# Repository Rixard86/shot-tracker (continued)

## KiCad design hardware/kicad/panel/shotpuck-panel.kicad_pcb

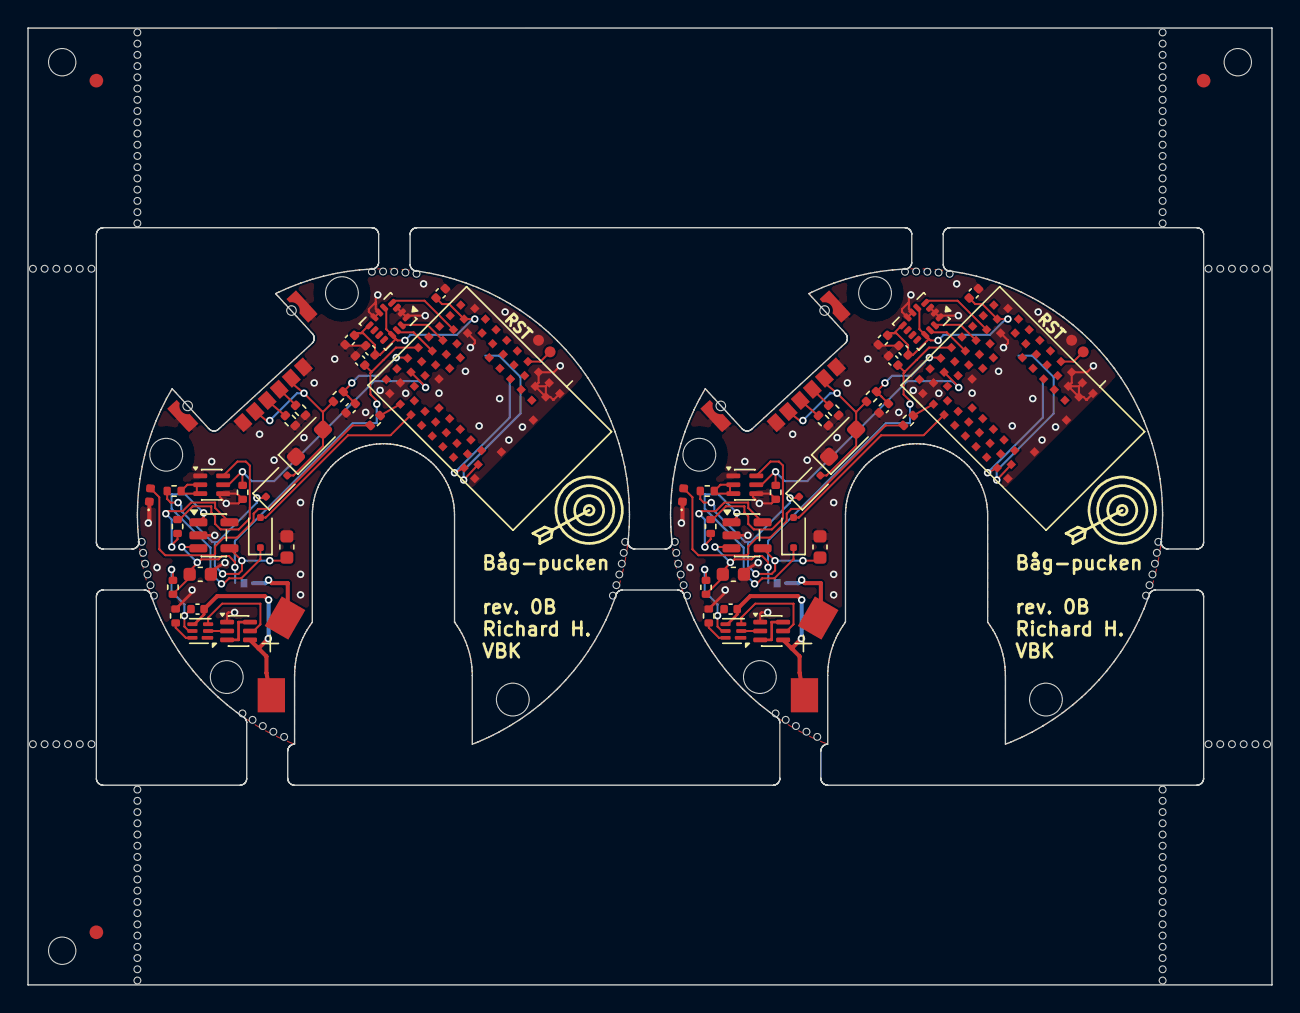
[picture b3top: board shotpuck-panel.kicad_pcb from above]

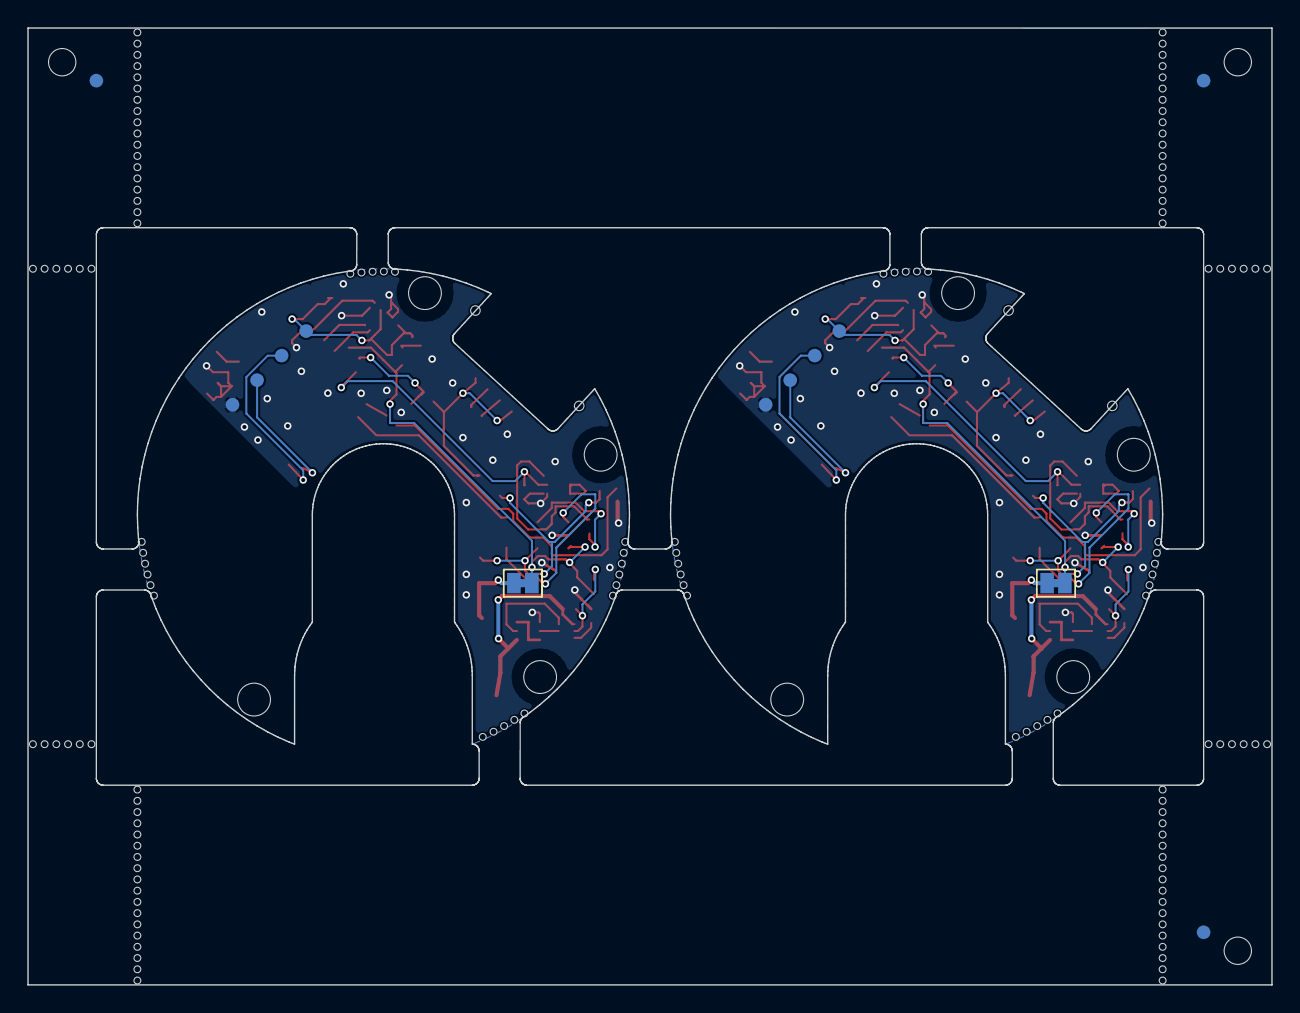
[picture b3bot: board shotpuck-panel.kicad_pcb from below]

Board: 2 copper layers, 91.0 x 70.0 mm, 221 parts (7 on the bottom side), 58 nets.

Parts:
BT1_0, BT1_1: LIR1254 (plain, spring contacts); LIR1254_Contacts_Edit
C1_0, C1_1: 4.7u 10V; C_0603_1608Metric
C2_0, C2_1: 10u 10V; C_0603_1608Metric
C3_0, C3_1, C4_0, C4_1: 4.7u 6.3V; C_0402_1005Metric
C6_0, C6_1, C7_0, C7_1, C8_0, C8_1, C9_0, C9_1: 100n; C_0402_1005Metric
D1_0, D1_1, D2_0, D2_1: BAT54J; D_SOD-323F
D3_0, D3_1: SMF5.0CA; D_SOD-123F
D4_0, D4_1: LED yellow-green 0402; LED_0402_1005Metric
H1_0, H1_1, H2_0, H2_1, H3_0, H3_1, H4_0, H4_1: M2; MountingHole_2.4mm_NPTH
J1_0, J1_1: TYPE-C 6PFS 2JCB1.6-H6.7 IPX8; USB_C_Receptacle_ShouHan_TYPE-C-6PFS-2JCB1.6-H6.7_IPX8
J2_0, J2_1: SWD pads; SWD_Pads_1x4_P2.54
JP1_0, JP1_1: I_MEAS (cut to measure); SolderJumper-2_P1.3mm_Bridged_Pad1.0x1.5mm
JP2_0, JP2_1: RESET pads; TweezerPads_2x0.8mm_Gap0.4mm
KiKit_FID_B_1, KiKit_FID_B_2, KiKit_FID_B_3: Fiducial
KiKit_FID_T_1, KiKit_FID_T_2, KiKit_FID_T_3: Fiducial
KiKit_MB_1_2, KiKit_MB_1_3, KiKit_MB_1_4, KiKit_MB_1_5, KiKit_MB_1_6, KiKit_MB_2_1, KiKit_MB_2_2, KiKit_MB_2_3, KiKit_MB_2_4, KiKit_MB_2_5, KiKit_MB_2_6, KiKit_MB_3_1, KiKit_MB_3_2, KiKit_MB_3_3, KiKit_MB_3_4, KiKit_MB_3_5, KiKit_MB_3_6, KiKit_MB_4_1, KiKit_MB_4_2, KiKit_MB_4_3, KiKit_MB_4_4, KiKit_MB_4_5, KiKit_MB_5_2, KiKit_MB_5_3, KiKit_MB_5_4, KiKit_MB_5_5, KiKit_MB_5_6, KiKit_MB_6_1, KiKit_MB_6_2, KiKit_MB_6_3, KiKit_MB_6_4, KiKit_MB_6_5, KiKit_MB_6_6, KiKit_MB_7_1, KiKit_MB_7_2, KiKit_MB_7_3, KiKit_MB_7_4, KiKit_MB_7_5, KiKit_MB_7_6, KiKit_MB_8_1, KiKit_MB_8_2, KiKit_MB_8_3, KiKit_MB_8_4, KiKit_MB_8_5, KiKit_MB_9_2, KiKit_MB_9_3, KiKit_MB_9_4, KiKit_MB_9_5, KiKit_MB_9_6, KiKit_MB_9_7, KiKit_MB_9_8, KiKit_MB_9_9, KiKit_MB_9_10, KiKit_MB_9_11, KiKit_MB_9_12, KiKit_MB_9_13, KiKit_MB_9_14, KiKit_MB_9_15, KiKit_MB_9_16, KiKit_MB_9_17, KiKit_MB_9_18, KiKit_MB_9_19, KiKit_MB_10_2, KiKit_MB_10_3, KiKit_MB_10_4, KiKit_MB_10_5, KiKit_MB_10_6, KiKit_MB_10_7, KiKit_MB_10_8, KiKit_MB_10_9, KiKit_MB_10_10, KiKit_MB_10_11, KiKit_MB_10_12, KiKit_MB_10_13, KiKit_MB_10_14, KiKit_MB_10_15, KiKit_MB_10_16, KiKit_MB_10_17, KiKit_MB_10_18, KiKit_MB_10_19, KiKit_MB_11_2, KiKit_MB_11_3, KiKit_MB_11_4, KiKit_MB_11_5, KiKit_MB_11_6, KiKit_MB_11_7, KiKit_MB_11_8, KiKit_MB_11_9, KiKit_MB_11_10, KiKit_MB_11_11, KiKit_MB_11_12, KiKit_MB_11_13, KiKit_MB_11_14, KiKit_MB_11_15, KiKit_MB_11_16, KiKit_MB_11_17, KiKit_MB_11_18, KiKit_MB_11_19, KiKit_MB_12_2, KiKit_MB_12_3, KiKit_MB_12_4, KiKit_MB_12_5, KiKit_MB_12_6, KiKit_MB_12_7, KiKit_MB_12_8, KiKit_MB_12_9, KiKit_MB_12_10, KiKit_MB_12_11, KiKit_MB_12_12, KiKit_MB_12_13, KiKit_MB_12_14, KiKit_MB_12_15, KiKit_MB_12_16, KiKit_MB_12_17, KiKit_MB_12_18, KiKit_MB_12_19, KiKit_MB_13_2, KiKit_MB_13_3, KiKit_MB_13_4, KiKit_MB_13_5, KiKit_MB_13_6, KiKit_MB_13_7, KiKit_MB_14_2, KiKit_MB_14_3, KiKit_MB_14_4, KiKit_MB_14_5, KiKit_MB_14_6, KiKit_MB_14_7, KiKit_MB_15_2, KiKit_MB_15_3, KiKit_MB_15_4, KiKit_MB_15_5, KiKit_MB_15_6, KiKit_MB_15_7, KiKit_MB_16_2, KiKit_MB_16_3, KiKit_MB_16_4, KiKit_MB_16_5, KiKit_MB_16_6, KiKit_MB_16_7: NPTH
KiKit_TO_1, KiKit_TO_2, KiKit_TO_3: NPTH
Q1_0, Q1_1: DMN63D8LDW; SOT-363_SC-70-6
Q2_0, Q2_1: DMN2004DWK; SOT-363_SC-70-6
R1_0, R1_1: 47k 1%; R_0402_1005Metric
R2_0, R2_1: 1M; R_0402_1005Metric
R3_0, R3_1: 100k; R_0402_1005Metric
R4_0, R4_1, R9_0, R9_1: 1k; R_0402_1005Metric
R7_0, R7_1: 330R; R_0402_1005Metric
R8_0, R8_1: 2.2k; R_0402_1005Metric
R10_0, R10_1, R11_0, R11_1: 5.1k 1%; R_0402_1005Metric
U1_0, U1_1: BMD-340-A-R; u-blox_BMD-340
U2_0, U2_1: LSM6DSV32XTR; LGA-14_3x2.5mm_P0.5mm_LayoutBorder3x4y
U3_0, U3_1: MCP73831T-2ACI/OT; SOT-23-5
U4_0, U4_1: BQ29700DSER; WSON-6_1.5x1.5mm_P0.5mm

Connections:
Board_0-/ACC_INT1: U1_0.19 (P0.03), U2_0.4 (INT1)
Board_0-/BAT_N: BT1_0.2 (-), C8_0.2, Q2_0.4 (S), U4_0.4 (VSS)
Board_0-/BAT_P: BT1_0.1 (+), JP1_0.1 (A)
Board_0-/BTN: JP2_0.1 (A), U1_0.7 (P0.26)
Board_0-/CC1: J1_0.A5 (CC1), R10_0.1
Board_0-/CC2: J1_0.B5 (CC2), R11_0.1
Board_0-/CHG_INH: Q1_0.5 (G), R3_0.1, U1_0.27 (P0.11)
Board_0-/CHG_STAT: D2_0.2 (A), U1_0.33 (P0.15)
Board_0-/GND: C1_0.2, C2_0.2, C3_0.2, C4_0.2, C6_0.2, C7_0.2, C9_0.2, D3_0.1 (A1), D4_0.1 (K), J1_0.A12 (GND), J1_0.B12 (GND), J1_0.SH (SHIELD), J2_0.4, JP2_0.2 (B), Q1_0.1 (S), Q1_0.4 (S), Q2_0.1 (S), R3_0.2, R8_0.2, R10_0.2, R11_0.2, U1_0.1 (GND), U1_0.2 (GND), U1_0.3 (GND), U1_0.4 (GND), U1_0.5 (GND), U1_0.16 (GND), U1_0.18 (GND), U1_0.29 (GND), U1_0.30 (GND), U1_0.45 (GND), U1_0.46 (GND), U1_0.47 (GND), U1_0.55 (GND), U2_0.1 (SDO/SA0), U2_0.2 (SDX), U2_0.3 (SCX), U2_0.6 (GND), U2_0.7 (GND), U3_0.2 (V_{SS})
Board_0-/LED_A: D4_0.2 (A), R4_0.2
Board_0-/LED_IO: R4_0.1, U1_0.31 (P0.13)
Board_0-/PCM_BAT: C8_0.1, R7_0.2, U4_0.5 (BAT)
Board_0-/PCM_COUT: Q2_0.2 (G), U4_0.2 (Cout)
Board_0-/PCM_D: Q2_0.3 (D), Q2_0.6 (D)
Board_0-/PCM_DOUT: Q2_0.5 (G), U4_0.3 (Dout)
Board_0-/PCM_VM: R8_0.1, U4_0.6 (V-)
Board_0-/PROG: R1_0.1, U3_0.5 (PROG)
Board_0-/PROG_SW: Q1_0.6 (D), R1_0.2
Board_0-/Q1_GATE: Q1_0.2 (G), Q1_0.3 (D), R2_0.2
Board_0-/SCL: U1_0.23 (P0.07), U2_0.13 (SCL)
Board_0-/SDA: U1_0.21 (P0.05), U2_0.14 (SDA)
Board_0-/STAT: D2_0.1 (K), U3_0.1 (STAT)
Board_0-/SWDCLK: J2_0.3, U1_0.43 (SWCLK)
Board_0-/SWDIO: J2_0.2, U1_0.44 (SWDIO)
Board_0-/VBAT: C2_0.1, C3_0.1, JP1_0.2 (B), R7_0.1, U1_0.65 (VCCH), U3_0.3 (V_{BAT})
Board_0-/VBUS_SNS: C9_0.1, R9_0.2, U1_0.66 (VBUS)
Board_0-/VDD: C4_0.1, C6_0.1, C7_0.1, J2_0.1, U1_0.17 (VCC), U2_0.5 (VDDIO), U2_0.8 (VDD), U2_0.12 (CS)
Board_0-/VIN: C1_0.1, D1_0.1 (K), R2_0.1, U3_0.4 (V_{DD})
Board_0-/VIN_RAW: D1_0.2 (A), D3_0.2 (A2), J1_0.A9 (VBUS), J1_0.B9 (VBUS), R9_0.1
Board_1-/ACC_INT1: U1_1.19 (P0.03), U2_1.4 (INT1)
Board_1-/BAT_N: BT1_1.2 (-), C8_1.2, Q2_1.4 (S), U4_1.4 (VSS)
Board_1-/BAT_P: BT1_1.1 (+), JP1_1.1 (A)
Board_1-/BTN: JP2_1.1 (A), U1_1.7 (P0.26)
Board_1-/CC1: J1_1.A5 (CC1), R10_1.1
Board_1-/CC2: J1_1.B5 (CC2), R11_1.1
Board_1-/CHG_INH: Q1_1.5 (G), R3_1.1, U1_1.27 (P0.11)
Board_1-/CHG_STAT: D2_1.2 (A), U1_1.33 (P0.15)
Board_1-/GND: C1_1.2, C2_1.2, C3_1.2, C4_1.2, C6_1.2, C7_1.2, C9_1.2, D3_1.1 (A1), D4_1.1 (K), J1_1.A12 (GND), J1_1.B12 (GND), J1_1.SH (SHIELD), J2_1.4, JP2_1.2 (B), Q1_1.1 (S), Q1_1.4 (S), Q2_1.1 (S), R3_1.2, R8_1.2, R10_1.2, R11_1.2, U1_1.1 (GND), U1_1.2 (GND), U1_1.3 (GND), U1_1.4 (GND), U1_1.5 (GND), U1_1.16 (GND), U1_1.18 (GND), U1_1.29 (GND), U1_1.30 (GND), U1_1.45 (GND), U1_1.46 (GND), U1_1.47 (GND), U1_1.55 (GND), U2_1.1 (SDO/SA0), U2_1.2 (SDX), U2_1.3 (SCX), U2_1.6 (GND), U2_1.7 (GND), U3_1.2 (V_{SS})
Board_1-/LED_A: D4_1.2 (A), R4_1.2
Board_1-/LED_IO: R4_1.1, U1_1.31 (P0.13)
Board_1-/PCM_BAT: C8_1.1, R7_1.2, U4_1.5 (BAT)
Board_1-/PCM_COUT: Q2_1.2 (G), U4_1.2 (Cout)
Board_1-/PCM_D: Q2_1.3 (D), Q2_1.6 (D)
Board_1-/PCM_DOUT: Q2_1.5 (G), U4_1.3 (Dout)
Board_1-/PCM_VM: R8_1.1, U4_1.6 (V-)
Board_1-/PROG: R1_1.1, U3_1.5 (PROG)
Board_1-/PROG_SW: Q1_1.6 (D), R1_1.2
Board_1-/Q1_GATE: Q1_1.2 (G), Q1_1.3 (D), R2_1.2
Board_1-/SCL: U1_1.23 (P0.07), U2_1.13 (SCL)
Board_1-/SDA: U1_1.21 (P0.05), U2_1.14 (SDA)
Board_1-/STAT: D2_1.1 (K), U3_1.1 (STAT)
Board_1-/SWDCLK: J2_1.3, U1_1.43 (SWCLK)
Board_1-/SWDIO: J2_1.2, U1_1.44 (SWDIO)
Board_1-/VBAT: C2_1.1, C3_1.1, JP1_1.2 (B), R7_1.1, U1_1.65 (VCCH), U3_1.3 (V_{BAT})
Board_1-/VBUS_SNS: C9_1.1, R9_1.2, U1_1.66 (VBUS)
Board_1-/VDD: C4_1.1, C6_1.1, C7_1.1, J2_1.1, U1_1.17 (VCC), U2_1.5 (VDDIO), U2_1.8 (VDD), U2_1.12 (CS)
Board_1-/VIN: C1_1.1, D1_1.1 (K), R2_1.1, U3_1.4 (V_{DD})
Board_1-/VIN_RAW: D1_1.2 (A), D3_1.2 (A2), J1_1.A9 (VBUS), J1_1.B9 (VBUS), R9_1.1
